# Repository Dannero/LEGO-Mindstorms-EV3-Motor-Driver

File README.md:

# LEGO Mindstorms EV3 Motor Driver

The following files are a part of my bachelor's thesis, in which I created custom motor driver PCBs with integrated microcontrollers, designed enclosures for these drivers, and created EV3-G blocks that allow the EV3 brick to communicate with the driver and carry out UART communication. 

---

### Driver_Arduino
This directory contains code for the [ev3dev](https://www.ev3dev.org/) OS and an Arduino Uno with an [Adafruit Motor Driver shield](https://learn.adafruit.com/adafruit-motor-shield/overview) and allows the EV3 with the ev3dev OS installed to control motors via I2C.

---

### Driver_V0.1
This directory contains the code for the first version of the custom driver in the `Driver_Code` directory, as well as PCB and 3D case files for manufacturing and printing. This PCB design is faulty and has some missing components, so I strongly advise to use the V0.2 driver.

---

### Driver_V0.2
Directory with source code and design files for the second iteration of the custom Driver, now more compact and able to run motors with higher performance, while being significantly more efficient in an idle state. 

---

### EV3-G_Blocks
Blocks for the *LEGO EV3 Lab Software* and their source code are situated in this directory. The `Thesis_Block.ev3b` allows the EV3 to communicate via the LEGO UART Sensor Protocol, built on the UART protocol, as well as control the motors connected to the motor driver via both I2C and the aforementioned UART-based protocols.

The `Dexter_Mod.ev3b` block is a modified version of the *Dexter Industries I2C Block*, available [here](https://github.com/DexterInd/EV3_Dexter_Industries_Sensors/blob/master/Dexter.ev3b). My modifications to this block fix the long-standing issue of the I2C communication functionality, where the maximum value of a sent byte is `0x7F`.

---

### Driver_Manual.pdf
This document contains all the necessary info to create the second version of the custom driver, get it up and running and use EV3-G block to control it.

---

### Future Work
The next iteration of the motor driver will take on a different approach, with the connection to the EV3 going wireless. Stay tuned!

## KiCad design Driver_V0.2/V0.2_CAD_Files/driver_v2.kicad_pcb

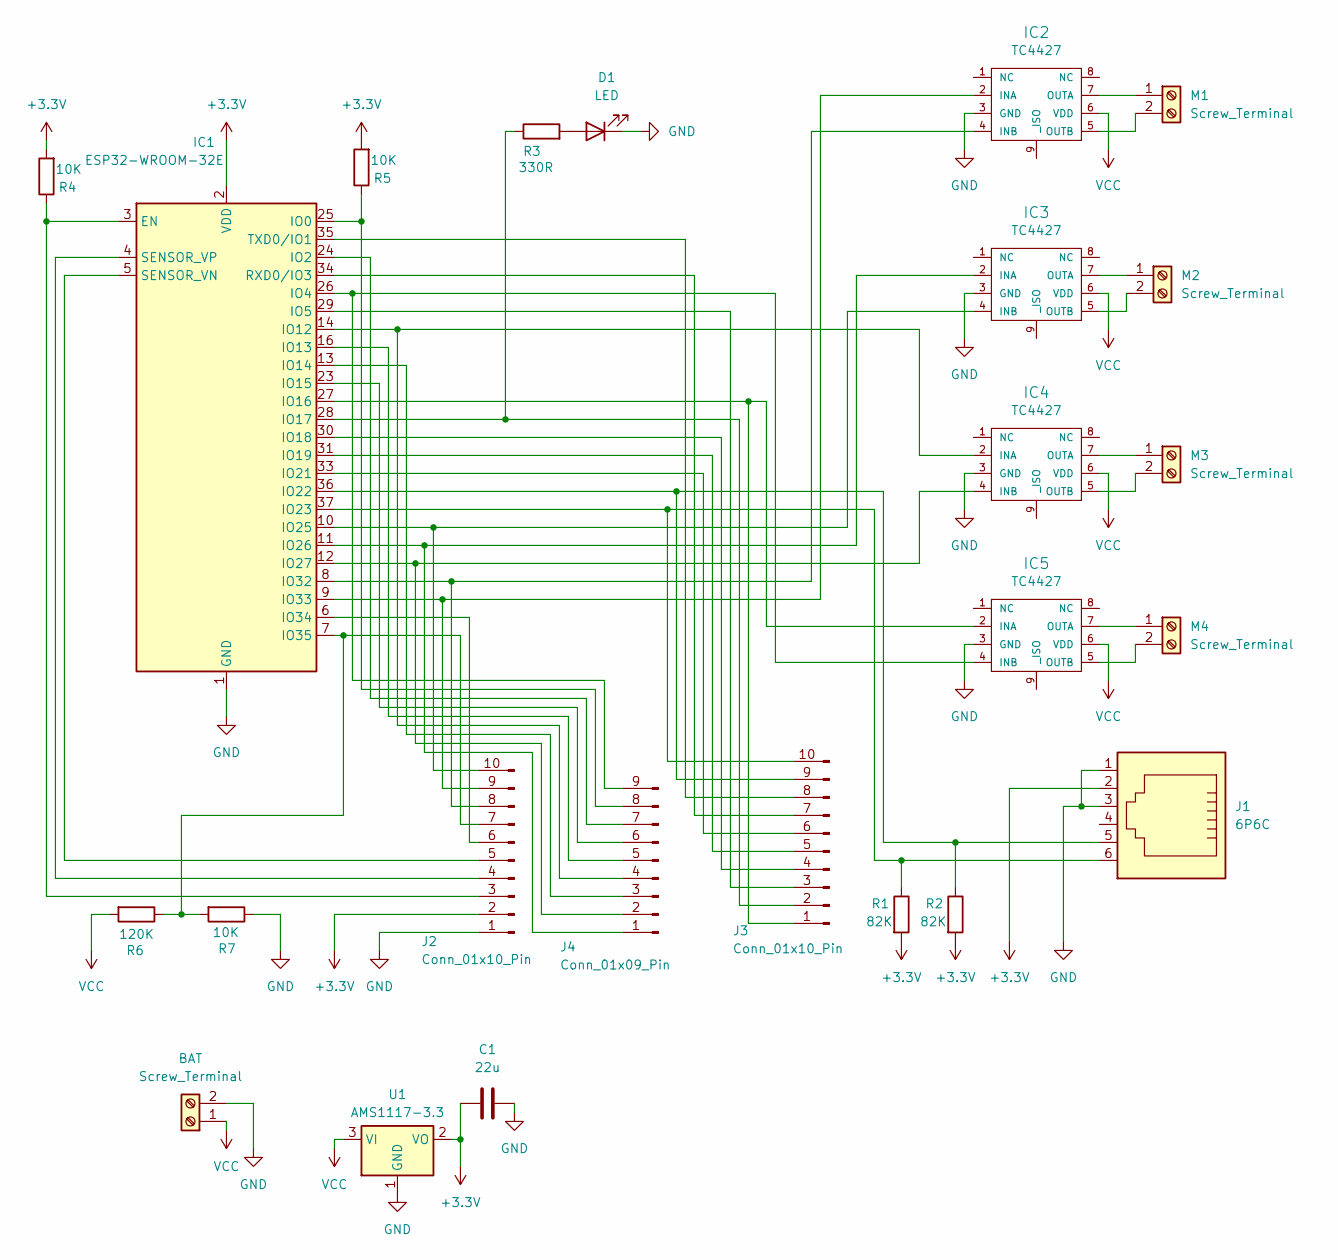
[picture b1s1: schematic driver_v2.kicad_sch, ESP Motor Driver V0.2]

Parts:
BAT: Screw_Terminal; TerminalBlock_MetzConnect_Type055_RT01502HDWU_1x02_P5.00mm_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
C1: 22u; C_1206_3216Metric_Pad1.33x1.80mm_HandSolder
D1: LED; LED_1206_3216Metric_Pad1.42x1.75mm_HandSolder
IC1: ESP32-WROOM-32E; ESP32-WROOM-32E-SMALL-KEEPOUT
IC2, IC3, IC4, IC5: TC4427; SOIC-8_3.9x4.9mm_P1.27mm
J1: 6P6C; RJ25_Wayconn_MJEA-660X1_Horizontal
J2, J3: Conn_01x10_Pin; PinHeader_1x10_P2.54mm_Vertical
J4: Conn_01x09_Pin; PinHeader_1x09_P2.54mm_Vertical
M1, M2, M3, M4: Screw_Terminal; TerminalBlock_MetzConnect_Type055_RT01502HDWU_1x02_P5.00mm_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
R1, R2: 82K; R_1206_3216Metric_Pad1.30x1.75mm_HandSolder
R3: 330R; R_1206_3216Metric_Pad1.30x1.75mm_HandSolder
R4, R5, R7: 10K; R_1206_3216Metric_Pad1.30x1.75mm_HandSolder
R6: 120K; R_1206_3216Metric_Pad1.30x1.75mm_HandSolder
U1: AMS1117-3.3; SOT-223-3_TabPin2

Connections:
+3.3V: C1.1, IC1.2 (VDD), J1.2, J2.2, R1.2, R2.2, R4.2, R5.2, U1.2 (VO)
GND: BAT.2, C1.2, D1.1 (K), IC1.1 (GND), IC1.15 (GND), IC1.38 (GND), IC1.39 (GND), IC2.3 (GND), IC3.3 (GND), IC4.3 (GND), IC5.3 (GND), J1.1, J1.3, J2.1, R7.1, U1.1 (GND); also elsewhere on the board
unnamed: D1.2 (A), R3.2
unnamed: IC1.3 (EN), J2.3, R4.1
unnamed: IC1.25 (IO0), J4.8, R5.1
unnamed: IC1.24 (IO2), J4.7
unnamed: IC1.26 (IO4), IC5.4 (INB), J4.9
unnamed: IC1.29 (IO5), J3.3
unnamed: IC1.14 (IO12), IC4.2 (INA), J4.4
unnamed: IC1.16 (IO13), J4.5
unnamed: IC1.13 (IO14), J4.3
unnamed: IC1.23 (IO15), J4.6
unnamed: IC1.27 (IO16), IC5.2 (INA), J3.1
unnamed: IC1.28 (IO17), J3.2, R3.1
unnamed: IC1.30 (IO18), J3.4
unnamed: IC1.31 (IO19), J3.5
unnamed: IC1.33 (IO21), J3.6
unnamed: IC1.36 (IO22), J1.5, J3.9, R2.1
unnamed: IC1.37 (IO23), J1.6, J3.10, R1.1
unnamed: IC1.10 (IO25), IC3.4 (INB), J2.10
unnamed: IC1.11 (IO26), IC3.2 (INA), J4.1
unnamed: IC1.12 (IO27), IC4.4 (INB), J4.2
unnamed: IC1.8 (IO32), IC2.4 (INB), J2.8
unnamed: IC1.9 (IO33), IC2.2 (INA), J2.9
unnamed: IC1.6 (IO34), J2.6
unnamed: IC1.7 (IO35), J2.7, R6.1, R7.2
unnamed: IC1.34 (RXD0/IO3), J3.7
unnamed: IC1.5 (SENSOR_VN), J2.5
unnamed: IC1.4 (SENSOR_VP), J2.4
unnamed: IC1.35 (TXD0/IO1), J3.8
unnamed: IC2.7 (OUTA), M1.1
unnamed: IC2.5 (OUTB), M1.2
unnamed: IC3.7 (OUTA), M2.1
unnamed: IC3.5 (OUTB), M2.2
unnamed: IC4.7 (OUTA), M3.1
unnamed: IC4.5 (OUTB), M3.2
unnamed: IC5.7 (OUTA), M4.1
unnamed: IC5.5 (OUTB), M4.2
VCC: BAT.1, IC2.6 (VDD), IC3.6 (VDD), IC4.6 (VDD), IC5.6 (VDD), R6.2, U1.3 (VI); also elsewhere on the board

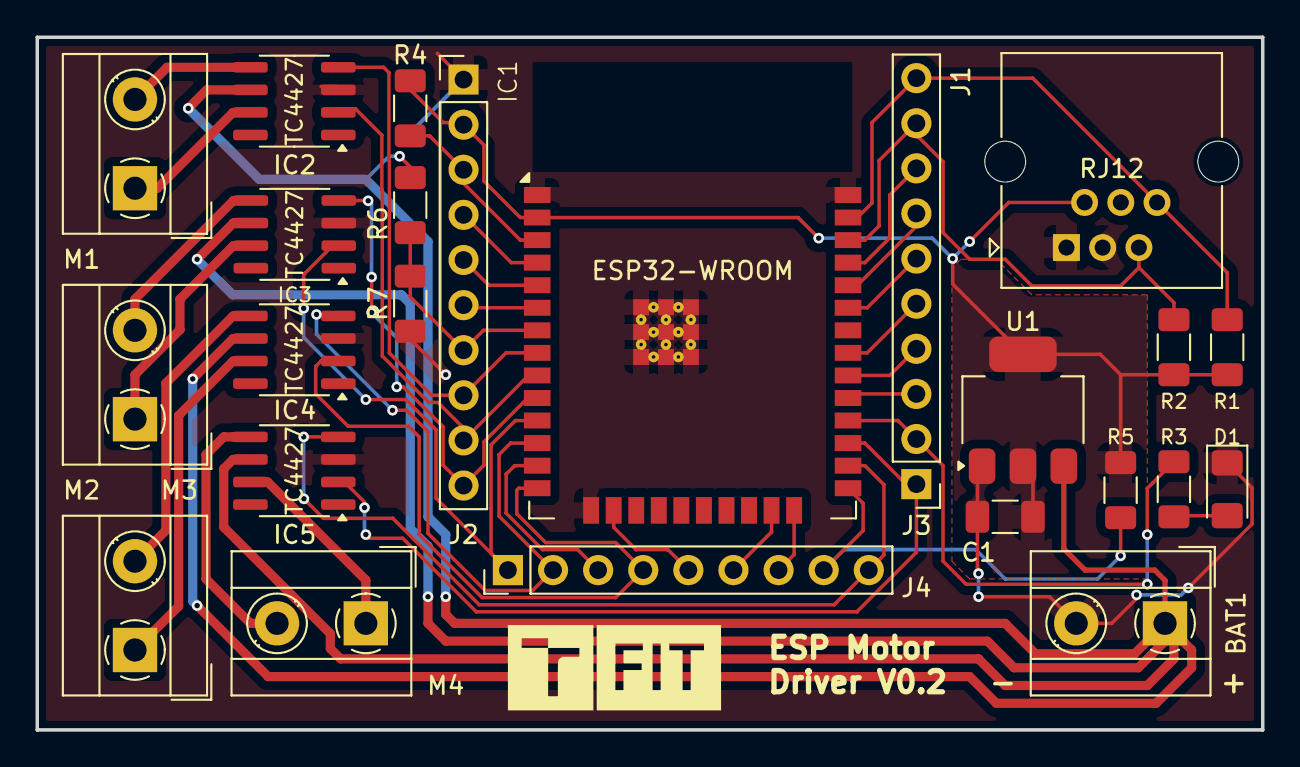
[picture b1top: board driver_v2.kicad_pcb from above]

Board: 2 copper layers, 69.0 x 39.0 mm, 24 parts (0 on the bottom side), 39 nets.

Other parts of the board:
BAT1: Screw_Terminal_01x02; TerminalBlock_MetzConnect_Type055_RT01502HDWU_1x02_P5.00mm_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

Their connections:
GND: BAT1.2; also elsewhere on the board
VCC: BAT1.1; also elsewhere on the board

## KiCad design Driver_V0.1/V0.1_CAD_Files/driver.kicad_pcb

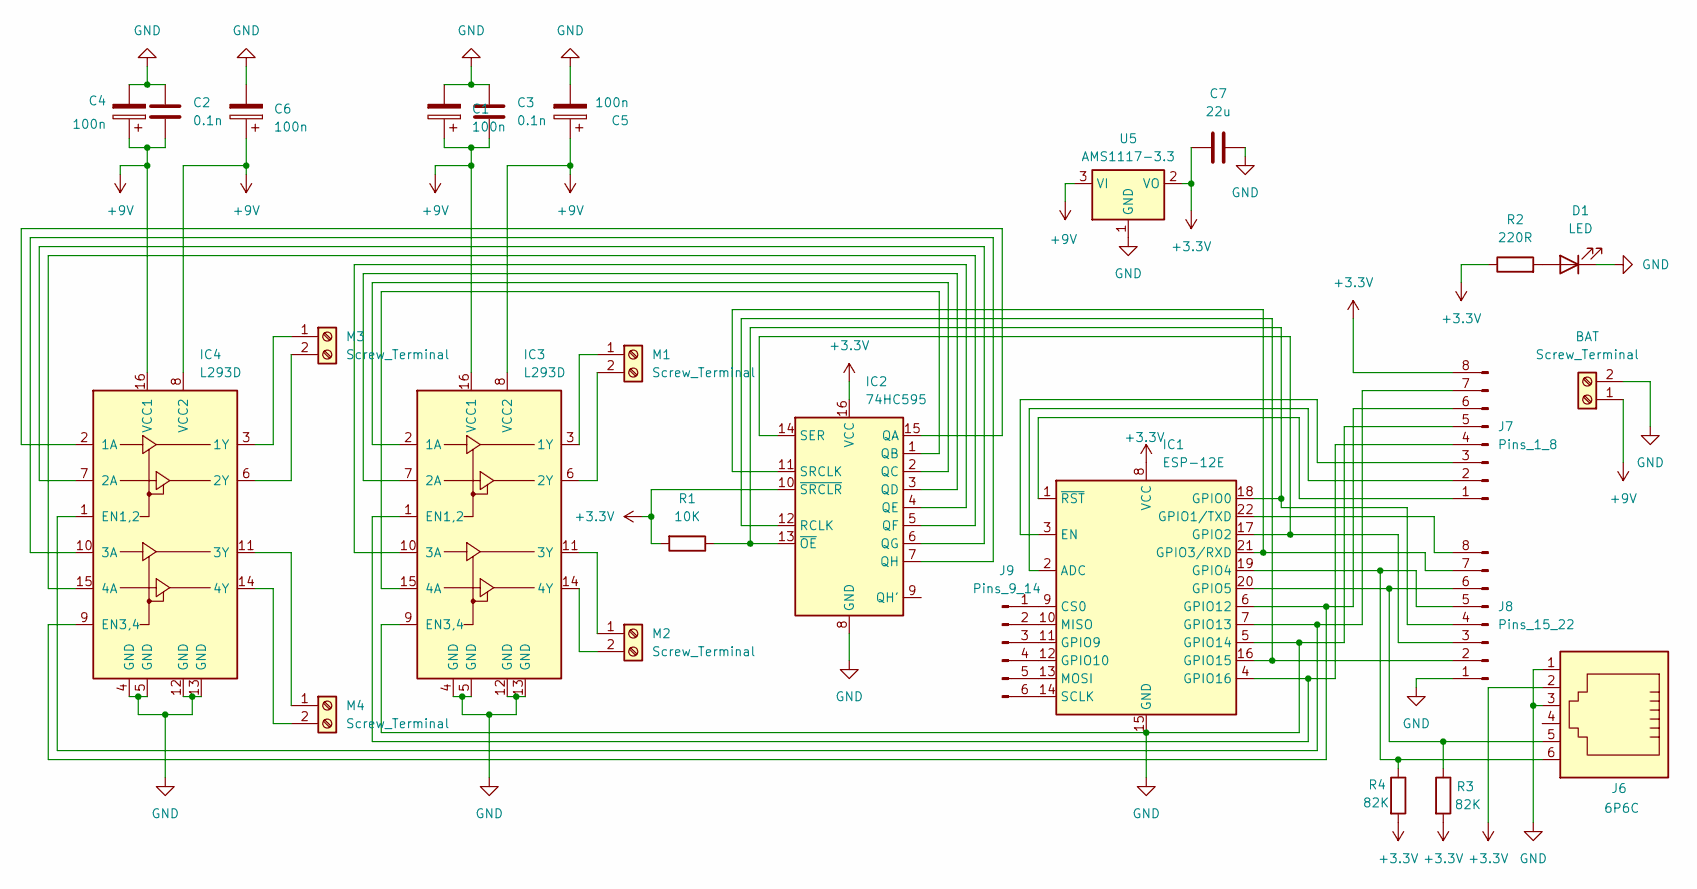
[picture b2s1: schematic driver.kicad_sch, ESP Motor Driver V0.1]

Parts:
BAT: Screw_Terminal; TerminalBlock_Altech_AK300-2_P5.00mm
C1, C4, C5, C6: 100n; C_1206_3216Metric_Pad1.33x1.80mm_HandSolder
C2, C3: 0.1n; C_1206_3216Metric_Pad1.33x1.80mm_HandSolder
C7: 22u; C_1206_3216Metric_Pad1.33x1.80mm_HandSolder
D1: LED; LED_1206_3216Metric_Pad1.42x1.75mm_HandSolder
IC1: ESP-12E
IC2: 74HC595; DIP-16_W7.62mm
IC3, IC4: L293D; DIP-16_W7.62mm
J6: 6P6C; RJ25_Wayconn_MJEA-660X1_Horizontal
J7: Pins_1_8; PinHeader_1x08_P2.54mm_Vertical
J8: Pins_15_22; PinHeader_1x08_P2.54mm_Vertical
J9: Pins_9_14; PinHeader_1x06_P2.54mm_Vertical
M1, M2, M3, M4: Screw_Terminal; TerminalBlock_Altech_AK300-2_P5.00mm
R1: 10K; R_1206_3216Metric_Pad1.30x1.75mm_HandSolder
R2: 220R; R_1206_3216Metric_Pad1.30x1.75mm_HandSolder
R3, R4: 82K; R_1206_3216Metric_Pad1.30x1.75mm_HandSolder
U5: AMS1117-3.3; SOT-223-3_TabPin2

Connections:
+3.3V: C7.1, IC1.8 (VCC), IC2.10 (~SRCLR), IC2.16 (VCC), J6.2, J7.8, R1.2, R2.1, R3.2, R4.2, U5.2 (VO); also elsewhere on the board
+9V: BAT.1, C1.1, C2.2, C3.2, C4.1, C5.1, C6.1, IC3.8 (VCC2), IC3.16 (VCC1), IC4.8 (VCC2), IC4.16 (VCC1), U5.3 (VI)
unnamed: D1.2 (A), R2.2
unnamed: IC1.2 (ADC), J7.2
unnamed: IC1.9 (CS0), J9.1
unnamed: IC1.3 (EN), J7.3
unnamed: IC1.18 (GPIO0), IC2.13 (~OE), J8.4, R1.1
unnamed: IC1.22 (GPIO1/TXD), J8.8
unnamed: IC1.17 (GPIO2), IC2.14 (SER), J8.3
unnamed: IC1.21 (GPIO3/RXD), IC2.11 (SRCLK), J8.7
unnamed 10: IC1.19 (GPIO4), J6.6, J8.5, R4.1; also elsewhere on the board
unnamed 11: IC1.20 (GPIO5), J6.5, J8.6, R3.1; also elsewhere on the board
unnamed: IC1.11 (GPIO9), J9.3
unnamed: IC1.12 (GPIO10), J9.4
unnamed: IC1.6 (GPIO12), IC4.9 (EN3,4), J7.6
unnamed: IC1.7 (GPIO13), IC4.1 (EN1,2), J7.7
unnamed: IC1.16 (GPIO15), IC2.12 (RCLK), J8.2
unnamed: IC1.4 (GPIO16), IC3.1 (EN1,2), J7.4
unnamed: IC1.10 (MISO), J9.2
unnamed: IC1.13 (MOSI), J9.5
unnamed: IC1.14 (SCLK), J9.6
unnamed: IC1.1 (~RST), J7.1
unnamed: IC2.15 (QA), IC4.2 (1A)
unnamed: IC2.1 (QB), IC3.15 (4A)
unnamed: IC2.2 (QC), IC3.2 (1A)
unnamed: IC2.3 (QD), IC3.7 (2A)
unnamed: IC2.4 (QE), IC3.10 (3A)
unnamed: IC2.5 (QF), IC4.15 (4A)
unnamed: IC2.6 (QG), IC4.7 (2A)
unnamed: IC2.7 (QH), IC4.10 (3A)
unnamed: IC3.3 (1Y), M1.1
unnamed: IC3.6 (2Y), M1.2
unnamed: IC3.11 (3Y), M2.1
unnamed: IC3.14 (4Y), M2.2
unnamed: IC4.3 (1Y), M3.1
unnamed: IC4.6 (2Y), M3.2
unnamed: IC4.11 (3Y), M4.1
unnamed: IC4.14 (4Y), M4.2

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
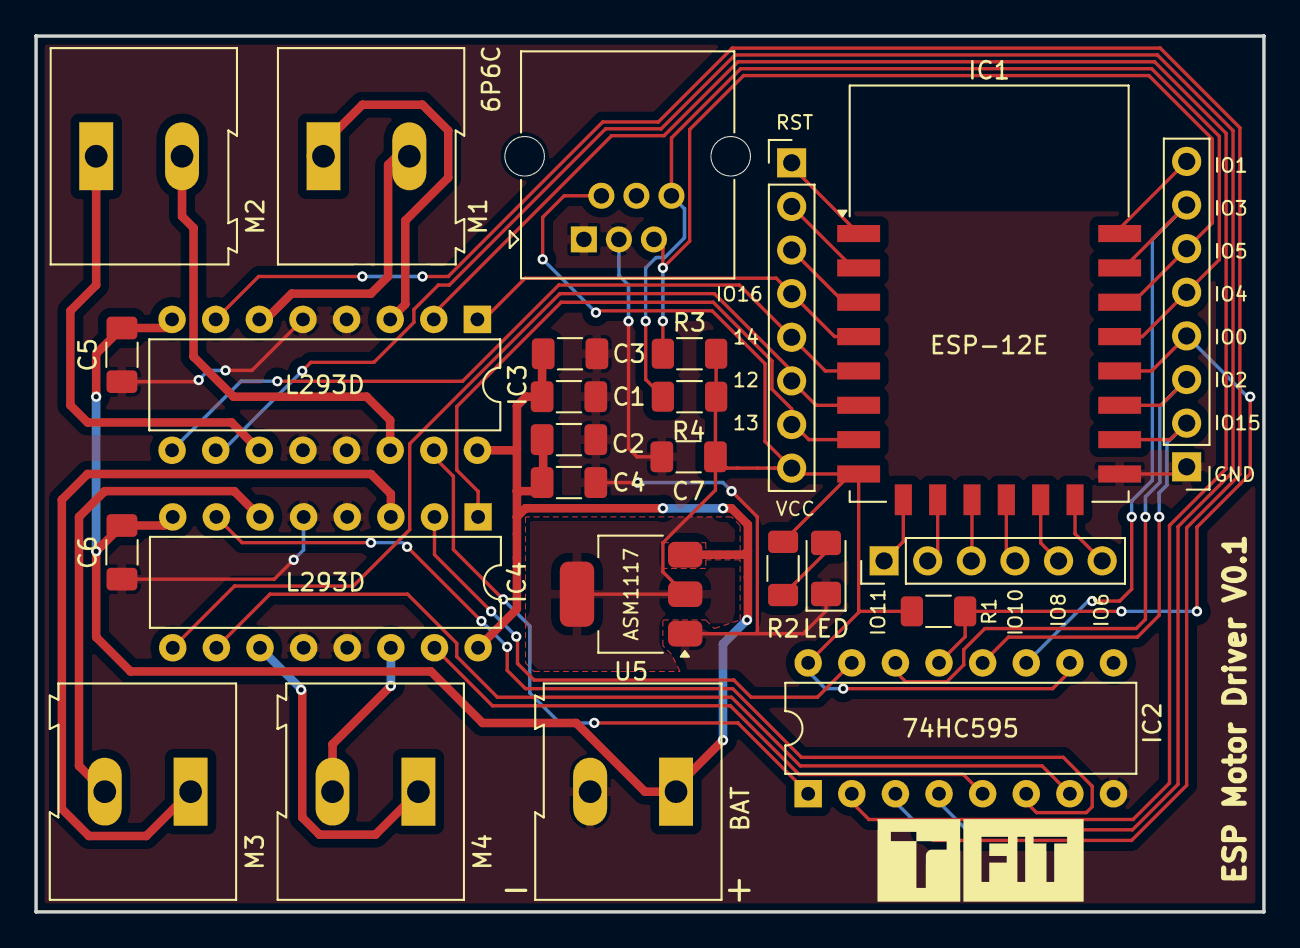
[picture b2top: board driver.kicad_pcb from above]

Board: 2 copper layers, 71.5 x 51.0 mm, 26 parts (0 on the bottom side), 40 nets.

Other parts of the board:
6P6C: 6P6C; RJ25_Wayconn_MJEA-660X1_Horizontal

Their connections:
+3.3V: 6P6C.2; also elsewhere on the board
unnamed 10: 6P6C.6; also elsewhere on the board
unnamed 11: 6P6C.5; also elsewhere on the board

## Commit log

2024-05-17 Publish Files
2024-06-25 Added patch file for the Dexter block modification
